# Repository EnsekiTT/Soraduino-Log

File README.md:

Soraduino-Log
=============

ロケット用の簡易ロガーのリポジトリ

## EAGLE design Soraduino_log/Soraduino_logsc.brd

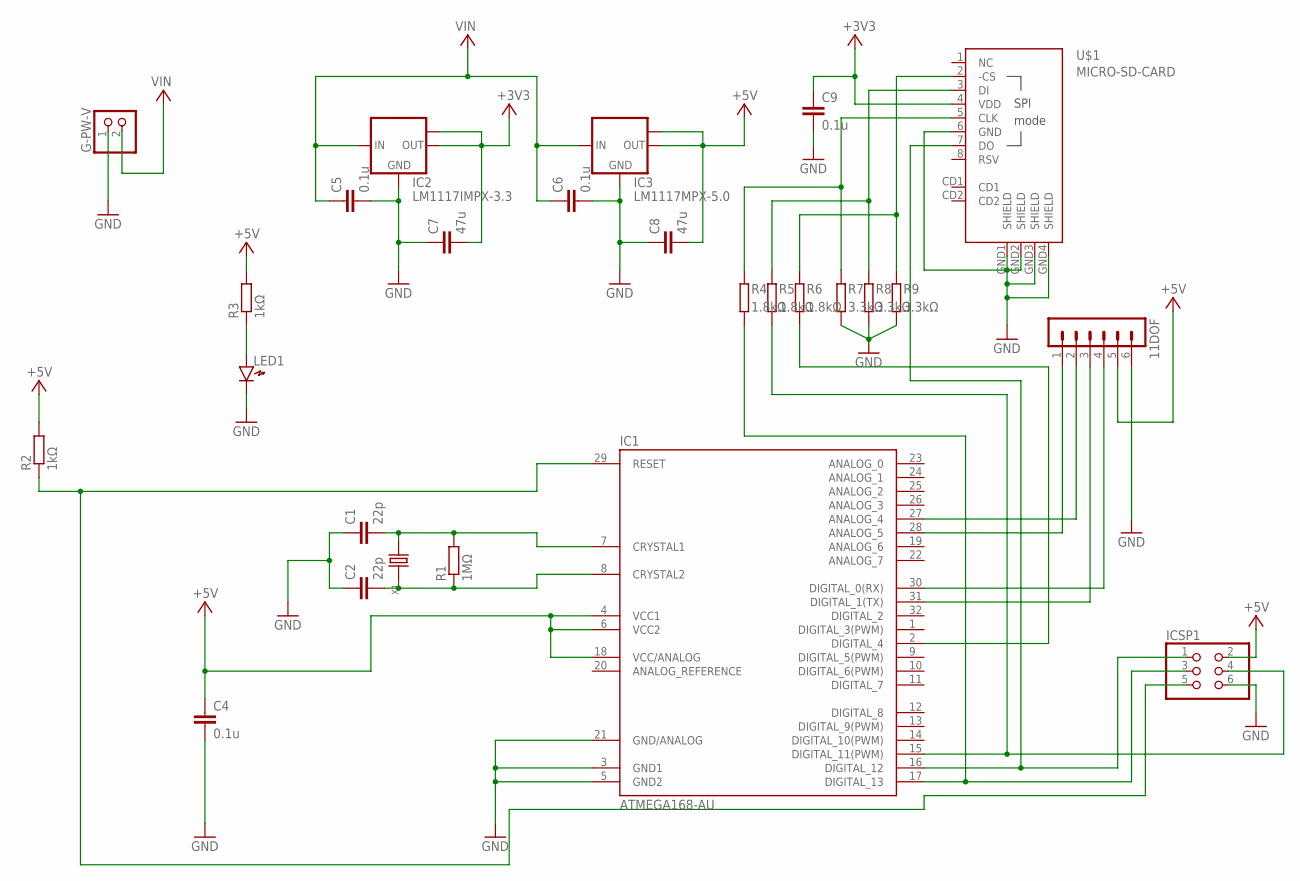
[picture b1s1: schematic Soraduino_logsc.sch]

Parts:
11DOF: MA06-1
C1, C2: 22p; C1608
C4, C5, C6, C9: 0.1u; C2012
C7, C8: 47u; C3225
G-PW-V: PINHD-1X2; 1X02
IC1: ATMEGA168-AU; TQFP32-08
IC2: LM1117IMPX-3.3; SOT223
IC3: LM1117MPX-5.0; SOT223
ICSP1: PINHD-2X3; 2X03
LED1: LED1608
R1: 1MΩ; R0603
R2, R3: 1kΩ; R0603
R4, R5, R6: 1.8kΩ; SMD1608
R7, R8, R9: 3.3kΩ; SMD1608
U$1: MICRO-SD-CARD; DM3AT-SF-PEJ
X1: CRYSTAL'3225'; 4P-SMD-3.2X2.5

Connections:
+3V3: C7.2, C9.1, IC2.2 (OUT), IC2.TAB (OUT1), U$1.4 (VDD)
+5V: 11DOF.5, C4.1, C8.2, IC1.4 (VCC1), IC1.6 (VCC2), IC1.18 (VCC/ANALOG), IC3.2 (OUT), IC3.TAB (OUT1), ICSP1.2, R2.2, R3.2
GND: 11DOF.6, C1.1, C2.1, C4.2, C5.2, C6.2, C7.1, C8.1, C9.2, G-PW-V.1, IC1.3 (GND1), IC1.5 (GND2), IC1.21 (GND/ANALOG), IC2.1 (GND), IC3.1 (GND), ICSP1.6, LED1.K, R7.2, R8.2, R9.2, U$1.6 (GND), U$1.GND1 (SHIELD), U$1.GND2 (SHIELD), U$1.GND3 (SHIELD), U$1.GND4 (SHIELD)
unnamed: C1.2, IC1.7 (CRYSTAL1), R1.2, X1.4 (2)
unnamed: C2.2, IC1.8 (CRYSTAL2), R1.1, X1.2 (1)
unnamed: 11DOF.1, IC1.28 (ANALOG_5)
unnamed: IC1.29 (RESET), ICSP1.5, R2.1
unnamed: 11DOF.4, IC1.30 (DIGITAL_0(RX))
unnamed: LED1.A, R3.1
unnamed: 11DOF.2, IC1.27 (ANALOG_4)
unnamed: R4.1, R7.1, U$1.5 (CLK)
unnamed: IC1.2 (DIGITAL_4), R6.2
unnamed: R5.1, R8.1, U$1.3 (DI)
unnamed: R6.1, R9.1, U$1.2 (-CS)
unnamed: IC1.15 (DIGITAL_11(PWM)), ICSP1.4, R5.2
unnamed: IC1.16 (DIGITAL_12), ICSP1.1, U$1.7 (DO)
unnamed: IC1.17 (DIGITAL_13), ICSP1.3, R4.2
unnamed: 11DOF.3, IC1.31 (DIGITAL_1(TX))
VCC: C5.1, C6.1, G-PW-V.2, IC2.3 (IN), IC3.3 (IN)

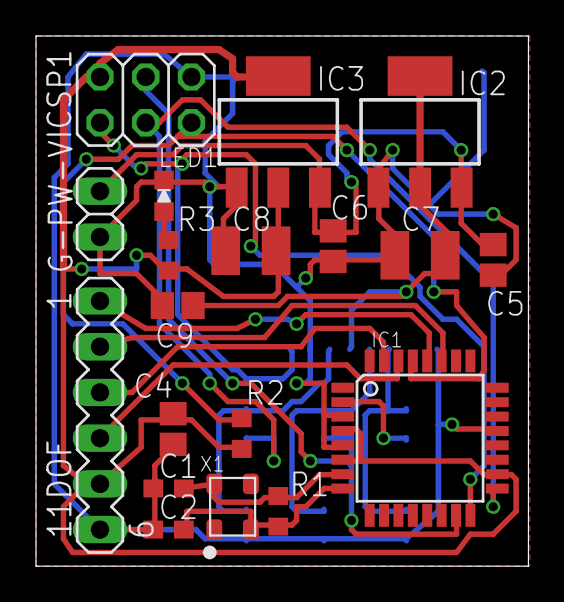
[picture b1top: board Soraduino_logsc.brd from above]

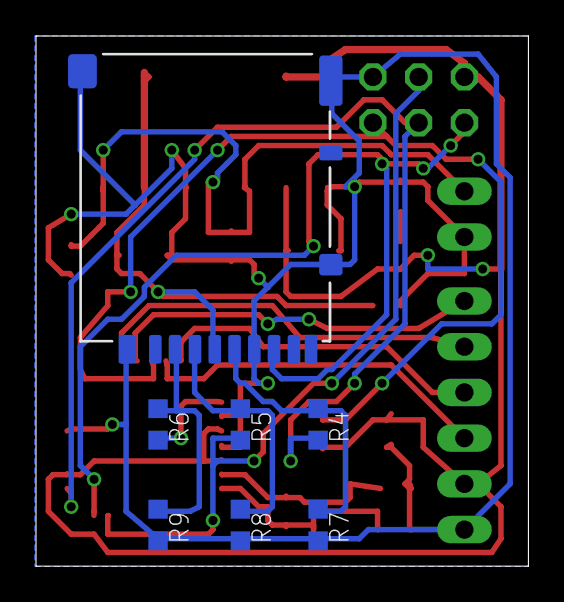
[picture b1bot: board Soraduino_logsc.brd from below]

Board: 2 copper layers, 27.4 x 29.5 mm, 26 parts (7 on the bottom side), 19 nets.

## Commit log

2013-06-09 add Arduino code. :SD,MPU6050,HMC5883L
2013-07-04 add code MS5611L
2013-07-29 add Soraduino_log Circuit
2013-08-11 fix I2C port mistake
2013-08-11 fix I2C port mistake about sch
2013-08-12 add .gitignore
